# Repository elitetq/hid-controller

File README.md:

# hid-controller

A custom USB gamepad built on an STM32F103, with a KiCad PCB and STM32 firmware. It has two analog sticks with click switches, a D-pad, face buttons, bumpers, digital triggers and Start/Share buttons.

https://github.com/user-attachments/assets/c4e4d3e5-b4be-487b-b6eb-255510382f0a

## USB identity and compatibility

The device appears as **J-Controller**, with manufacturer **Jonart B** and VID:PID **1209:028e**. It sends custom HID gamepad reports. The controls follow an Xbox-style layout, but the firmware does not provide native XInput support.

Linux enumerates the controller. Windows only partly enumerates it so far. You can try [x360ce](https://www.x360ce.com/) for XInput mapping, but Windows needs to detect the controller first. There is no confirmed setup procedure for Windows yet.

## Files

| Path | Purpose |
| --- | --- |
| [hid-controller-pcb/](hid-controller-pcb/) | KiCad schematic, PCB, libraries and BOM |
| `hid-controller-pcb/production/hid-controller-pcb.zip` | Fabrication Gerbers |
| `hid-controller-code/hid-controller-code/` | Active firmware and Makefile |
| `Core/Src/main.c` inside the firmware folder | ADC sampling, button mapping and report updates |
| `USB_DEVICE/App/` inside the firmware folder | USB descriptors and HID interface |
| `usb-backup/` inside the firmware folder | Older firmware copy; not the Makefile's source tree |
| `assets/` | Photos, PCB layout and video |

## PCB and assembly

Open `hid-controller-pcb/hid-controller-pcb.kicad_pro` in KiCad. Review the schematic and layout before fabrication. The root board BOM is `hid-controller-pcb/BOM.csv`; production exports also include `production/bom.csv` and `production/positions.csv`. Match the BOM and placement export to the board revision you intend to assemble.

Use the schematic's **SWDIO**, **SWCLK** and ground nets for the ST-Link connection, together with target-voltage reference as required by your probe. Check the actual connector orientation against the schematic rather than assuming a standard header pin order.

## Build

Requires GNU make, Arm GNU tools (`arm-none-eabi-gcc`, `objcopy` and `size`, including the C library/nano specs), and a POSIX shell for Makefile commands. Flashing requires ST-Link and [STM32CubeProgrammer](https://www.st.com/en/development-tools/stm32cubeprog.html), with `STM32_Programmer_CLI` on PATH.

**NOTE:** The firmware folder contains both `STM32F103XX_FLASH.ld` and `STM32F103xx_FLASH.ld`. They collide on a normal Windows filesystem. Use a case-sensitive filesystem (for example, a clone inside WSL's Linux filesystem) so both files can be checked out. The Makefile selects `STM32F103xx_FLASH.ld`.

```sh
git clone https://github.com/elitetq/hid-controller.git
cd hid-controller/hid-controller-code/hid-controller-code
make clean
make
```

The compiler path defaults to `/usr/bin/`. If your toolchain is elsewhere:

```sh
make GCC_PATH=/path/to/arm-toolchain/bin
```

Or, if the Arm tools are already on PATH, use `make GCC_PATH=`. The output is `build/hid-controller-code.elf`, with `.hex` and `.bin` versions alongside it. Clean first so checked-in build artifacts are not reused. There is no specific compiler/programmer version recorded for this build.

## Flash

Connect ST-Link to the powered target with common ground. From the firmware folder:

```sh
STM32_Programmer_CLI -c port=SWD -w build/hid-controller-code.elf -v -rst
```

This writes the ELF, verifies it and resets the device. The Makefile's `make flash` target contains a machine-specific Windows programmer path; use the command above or override `STMJLINKPATH` with your programmer executable. If you build in WSL, make sure the programmer can access ST-Link. You can also copy the ELF to Windows and flash it with STM32CubeProgrammer there.

## Check the inputs

1. Connect the controller's USB data port to the host. On Linux, `lsusb -d 1209:028e` can check enumeration; then check the inputs separately.
2. Open a gamepad input viewer. On Windows, start with **Win+R > joy.cpl** if the device appears there.
3. Move both sticks through their range and back to center. Check the D-pad, face buttons, bumpers, Start/Share and both stick clicks individually.
4. Press and release each trigger. These are digital switches: the firmware maps each trigger to 0 or 255, not an analog pressure range.
5. If using x360ce, confirm it detects the source device before mapping controls to a virtual controller and testing in a game. Failure to enumerate must be solved before mapping can help.

If inputs are missing, compare `gamepad_update_buttons()` and `gamepad_update_joysticks()` in `Core/Src/main.c` with the schematic and the report descriptor in `USB_DEVICE/App/usbd_custom_hid_if.c`. The two stick axes are swapped/inverted in software. Check the inputs on the assembled controller, as enumeration alone does not confirm that the mappings work.

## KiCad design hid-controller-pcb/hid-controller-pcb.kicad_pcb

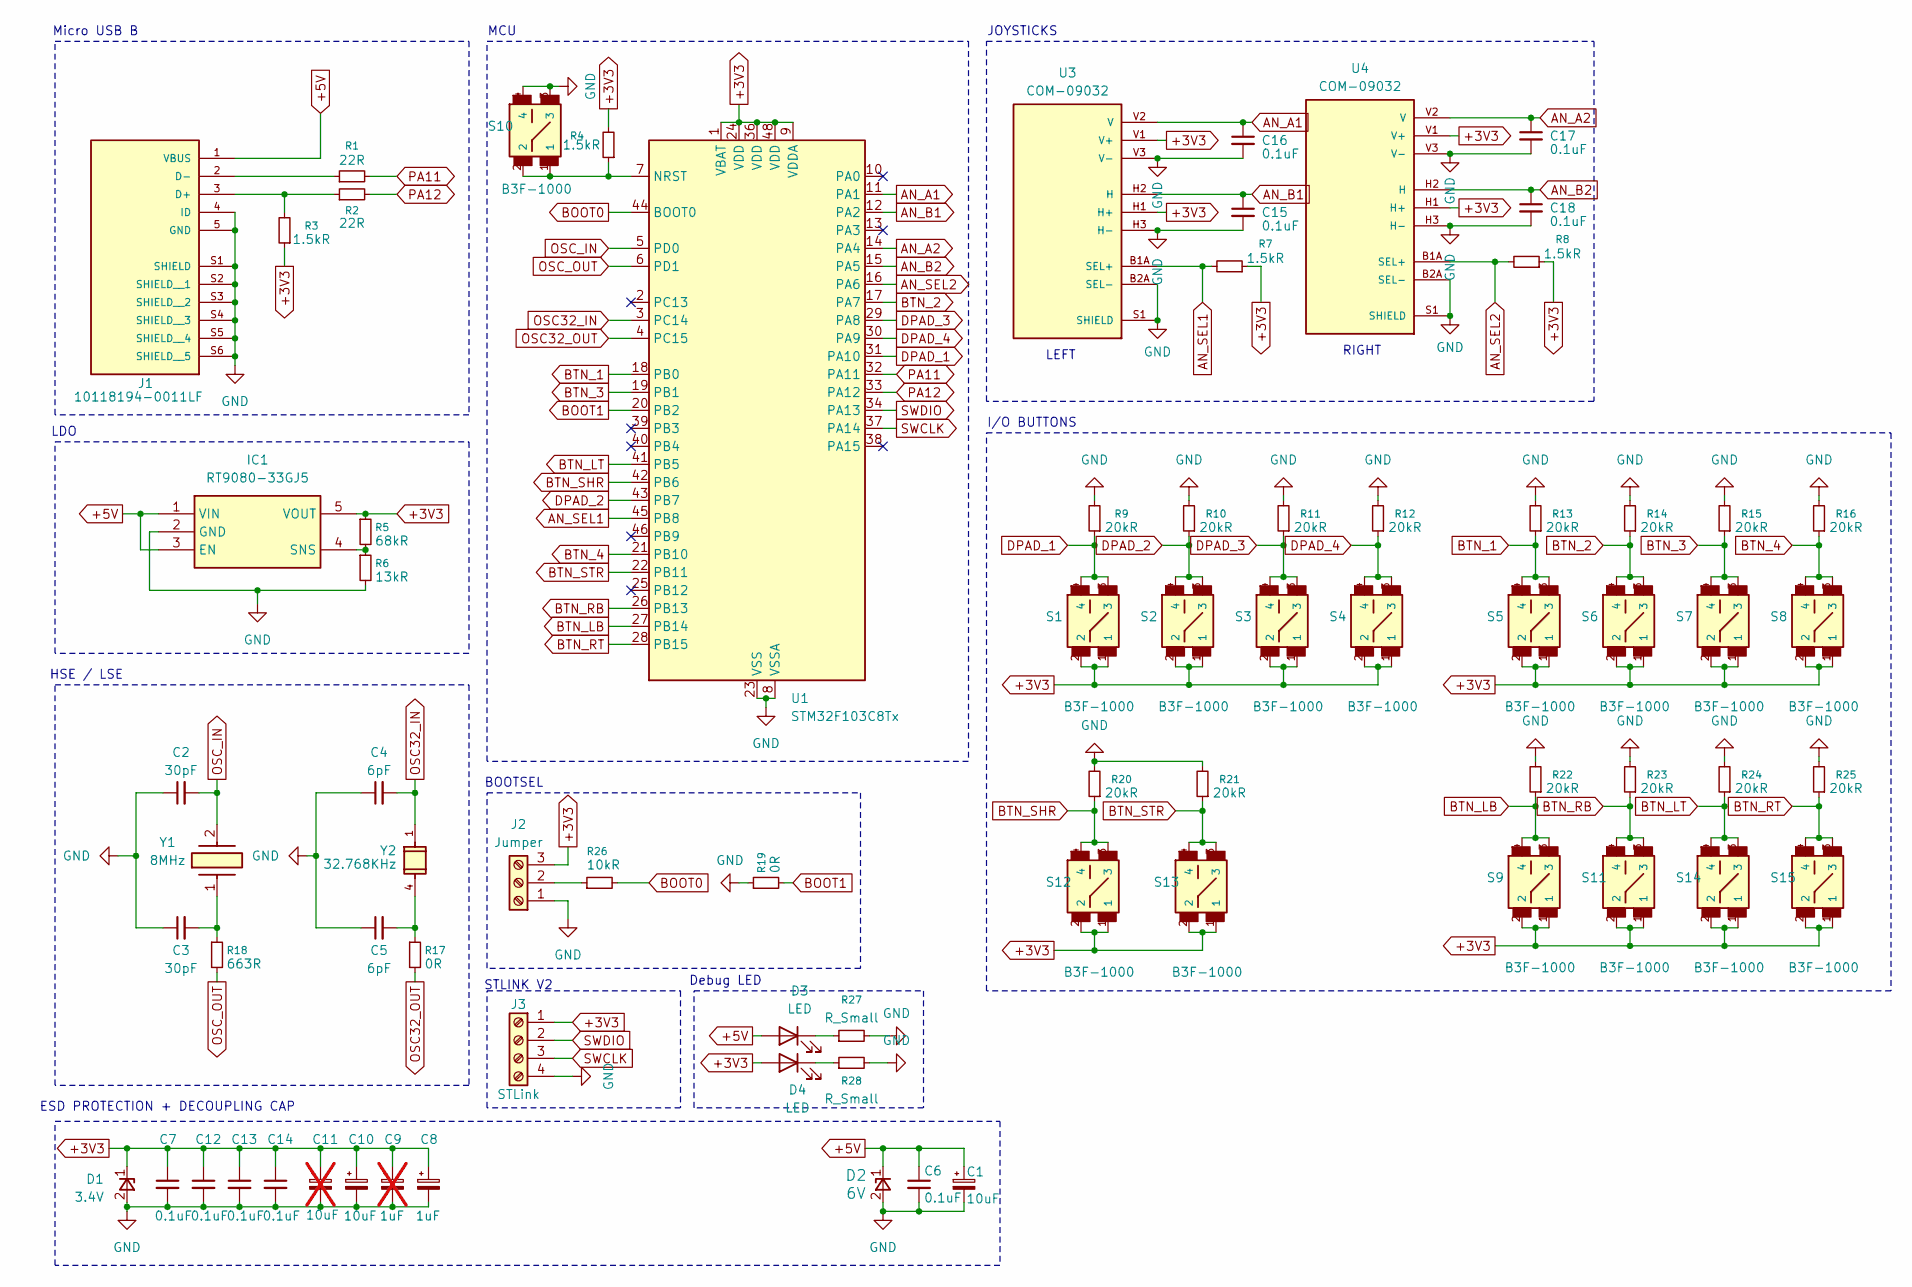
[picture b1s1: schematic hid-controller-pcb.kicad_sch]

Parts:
C1, C10: 10uF; CAPAE530X550N
C2, C3: 30pF; C_0603_1608Metric
C4, C5: 6pF; C_0603_1608Metric
C6, C7, C12, C13, C14: 0.1uF; C_0603_1608Metric
C8: 1uF; C_0603_1608Metric
C9: 1uF; C_0603_1608Metric; not fitted
C11: 10uF; CAPAE530X550N; not fitted
C15, C16, C17, C18: 0.1uF; C_0805_2012Metric_Pad1.18x1.45mm_HandSolder
D1: 3.4V; SMFA2005CA; Manufacturer_Part_Number SMF3.3; Mouser Part Number 576-SMF3.3
D2: 6V; DIODE_VESD05A1B-HD1-GS08_VIS
D3, D4: LED; LED_0805_2012Metric
IC1: RT9080-33GJ5; Manufacturer_Part_Number RT9080-33GJ5; Mouser Part Number 835-RT9080-33GJ5
J1: 10118194-0011LF; PARTREV D
J2: Jumper; PinHeader_1x03_P2.54mm_Vertical
J3: STLink; PinHeader_1x04_P2.54mm_Vertical
R1, R2: 22R; R_0805_2012Metric_Pad1.20x1.40mm_HandSolder
R3, R4, R7, R8: 1.5kR; R_0603_1608Metric
R5: 68kR; R_0603_1608Metric
R6: 13kR; R_0603_1608Metric
R9, R10, R11, R12, R13, R14, R15, R16, R20, R21, R22, R23, R24, R25: 20kR; R_0603_1608Metric
R17, R19: 0R; R_0603_1608Metric
R18: 663R; R_0603_1608Metric
R26: 10kR; R_0805_2012Metric_Pad1.20x1.40mm_HandSolder
R27, R28: R_Small; R_0805_2012Metric_Pad1.20x1.40mm_HandSolder
S1, S2, S3, S4, S5, S6, S7, S8, S9, S10, S11, S12, S13, S14, S15: B3F-1000; SW_B3F-1000
U1: STM32F103C8Tx; LQFP-48_7x7mm_P0.5mm
U3, U4: COM-09032; XDCR_COM-09032; PARTREV N/A
Y1: 8MHz; ABLS-8.000MHZ-B4-T; Manufacturer_Part_Number ABLS-8.000MHZ-B4-T; Mouser Part Number 815-ABLS-8.0M-T
Y2: 32.768KHz; XTAL_ABS25-32.768KHZ-6-T

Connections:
+3V3: C7.1, C8.1, C9.1, C10.1, C11.1, C12.1, C13.1, C14.1, D1.1 (K), D4.2 (A), IC1.5 (VOUT), J2.3, J3.1, R3.1, R4.2, R5.1, R7.1, R8.1, S1.1, S1.2, S2.1, S2.2, S3.1, S3.2, S4.1, S4.2, S5.1, S5.2, S6.1, S6.2, S7.1, S7.2, S8.1, S8.2, S9.1, S9.2, S11.1, S11.2, S12.1, S12.2, S13.1, S13.2, S14.1, S14.2, S15.1, S15.2, U1.1 (VBAT), U1.9 (VDDA), U1.24 (VDD), U1.36 (VDD), U1.48 (VDD), U3.H1 (H+), U3.V1 (V+), U4.H1 (H+), U4.V1 (V+)
+5V: C1.1, C6.1, D2.1, D3.2 (A), IC1.1 (VIN), IC1.3 (EN), J1.1 (VBUS)
AN_A1: C16.1, U1.11 (PA1), U3.V2 (V)
AN_A2: C17.1, U1.14 (PA4), U4.V2 (V)
AN_B1: C15.1, U1.12 (PA2), U3.H2 (H)
AN_B2: C18.1, U1.15 (PA5), U4.H2 (H)
AN_SEL1: R7.2, U1.45 (PB8), U3.B1A (SEL+)
AN_SEL2: R8.2, U1.16 (PA6), U4.B1A (SEL+)
BOOT0: R26.2, U1.44 (BOOT0)
BOOT1: R19.2, U1.20 (PB2)
BTN_1: R13.1, S5.3, S5.4, U1.18 (PB0)
BTN_2: R14.1, S6.3, S6.4, U1.17 (PA7)
BTN_3: R15.1, S7.3, S7.4, U1.19 (PB1)
BTN_4: R16.1, S8.3, S8.4, U1.21 (PB10)
BTN_LB: R22.1, S9.3, S9.4, U1.27 (PB14)
BTN_LT: R24.1, S14.3, S14.4, U1.41 (PB5)
BTN_RB: R23.1, S11.3, S11.4, U1.26 (PB13)
BTN_RT: R25.1, S15.3, S15.4, U1.28 (PB15)
BTN_SHR: R20.1, S12.3, S12.4, U1.42 (PB6)
BTN_STR: R21.1, S13.3, S13.4, U1.22 (PB11)
DPAD_1: R9.1, S1.3, S1.4, U1.31 (PA10)
DPAD_2: R10.1, S2.3, S2.4, U1.43 (PB7)
DPAD_3: R11.1, S3.3, S3.4, U1.29 (PA8)
DPAD_4: R12.1, S4.3, S4.4, U1.30 (PA9)
GND: C1.2, C2.1, C3.1, C4.1, C5.1, C6.2, C7.2, C8.2, C9.2, C10.2, C11.2, C12.2, C13.2, C14.2, C15.2, C16.2, C17.2, C18.2, D1.2 (A), D2.2, IC1.2 (GND), J1.4 (ID), J1.5 (GND), J1.S1 (SHIELD), J1.S2 (SHIELD__1), J1.S3 (SHIELD__2), J1.S4 (SHIELD__3), J1.S5 (SHIELD__4), J1.S6 (SHIELD__5), J2.1, J3.4, R6.2, R9.2, R10.2, R11.2, R12.2, R13.2, R14.2, R15.2, R16.2, R19.1, R20.2, R21.2, R22.2, R23.2, R24.2, R25.2, R27.2, R28.2, S10.3, S10.4, U1.8 (VSSA), U1.23 (VSS), U1.35 (VSS), U1.47 (VSS), U3.B2A (SEL-), U3.H3 (H-), U3.S1 (SHIELD), U3.S2 (SHIELD), U3.S3 (SHIELD), U3.S4 (SHIELD), U3.V3 (V-), U4.B2A (SEL-), U4.H3 (H-), U4.S1 (SHIELD), U4.S2 (SHIELD), U4.S3 (SHIELD), U4.S4 (SHIELD), U4.V3 (V-)
unnamed: C3.2, R18.1, Y1.1
unnamed: C5.2, R17.1, Y2.4
unnamed: D3.1 (K), R27.1
unnamed: D4.1 (K), R28.1
unnamed: IC1.4 (SNS), R5.2, R6.1
unnamed: J1.3 (D+), R2.1, R3.2
unnamed: J1.2 (D-), R1.1
unnamed: J2.2, R26.1
unnamed: R4.1, S10.1, S10.2, U1.7 (NRST)
OSC32_IN: C4.2, U1.3 (PC14), Y2.1
OSC32_OUT: R17.2, U1.4 (PC15)
OSC_IN: C2.2, U1.5 (PD0), Y1.2
OSC_OUT: R18.2, U1.6 (PD1)
PA11: R1.2, U1.32 (PA11)
PA12: R2.2, U1.33 (PA12)
SWCLK: J3.3, U1.37 (PA14)
SWDIO: J3.2, U1.34 (PA13)

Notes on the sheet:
MCU
Micro USB B
BOOTSEL
HSE / LSE
Debug LED
STLINK V2
RIGHT
LDO
LEFT
JOYSTICKS
I/O BUTTONS
ESD PROTECTION + DECOUPLING CAP

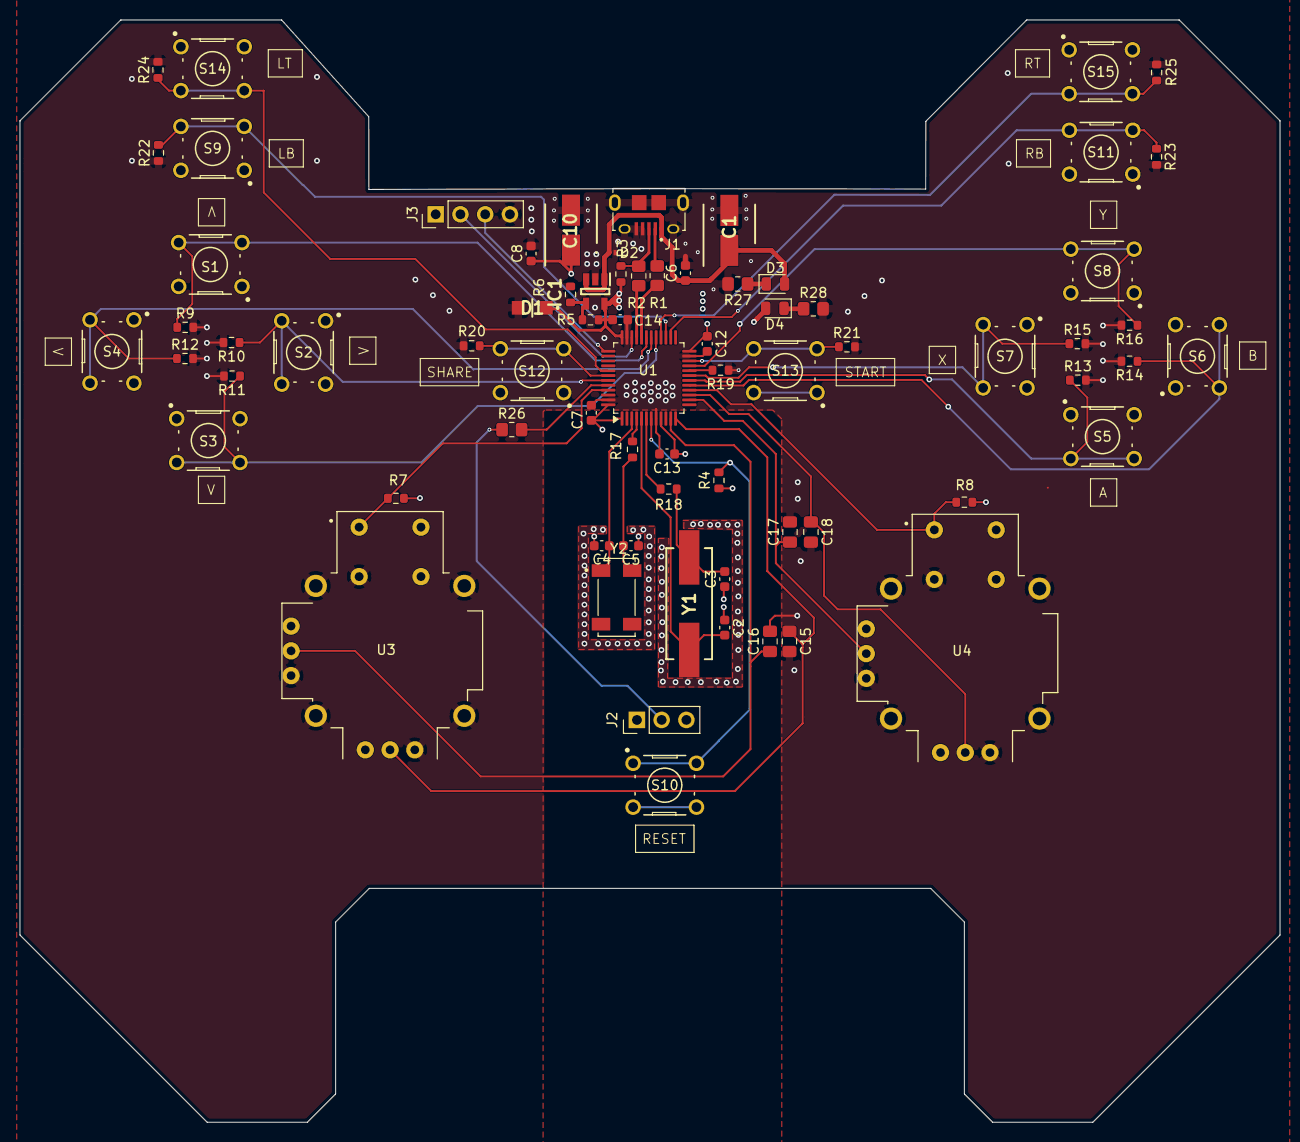
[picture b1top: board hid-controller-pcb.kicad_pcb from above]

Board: 4 copper layers, 129.3 x 113.2 mm, 72 parts (0 on the bottom side), 42 nets.

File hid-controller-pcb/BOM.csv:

Reference,Value,MPN,QTY
"C8,C9,C10,C11",10uF,CAPAE530X550N,4
"C2,C3",30pF,06031U300GAT2A,2
"C4,C5",6pF,CBR06C609CAGAC,2
"C6,C7,C12,C13,C14",0.1uF,C0603C104K5RACTU,5
D1,3.4V,SMF3.3,1
D2,6V,VESD05A1B-HD1-GS08,1
IC1,RT9080-33GJ5,RT9080-33GJ5,1
J1,10118194-0011LF,10118194-0011LF,1
J2,Jumper,PRPC003SAAN-RC,1
"R1,R2",22R,RC0805FR-0722RL,2
"R3,R4,R7,R8",1.5kR,RMCF0603FT1K50,4
R5,68kR,RC0603FR-0768KL,1
R6,13kR,RMCF0603FT13K0,1
"R9,R10,R11,R12,R13,R14,R15,R16",20kR,RC0603FR-0720KL,8
"R17,R19",0R,RC0603JR-070RL,2
R18,663R,RC0603FR-07665RL,1
"S1,S2,S3,S4,S5,S6,S7,S8,S10",B3F-1000,B3F-1000,12
U1,STM32F103C8Tx,STM32F103C8Tx,1
"U3,U4",COM-09032,9032,2
Y1,8MHz,ABLS-8.000MHZ-B4-T,1
Y2,32.768KHz,ABS25-32.768KHZ-6-T,1
C1,1uF,UMK107AB7105KA-T,1
,jumper short,QPC02SXGN-RC,1

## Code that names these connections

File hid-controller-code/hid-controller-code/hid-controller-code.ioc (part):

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Mcu.Name=STM32F103C(8-B)Tx
Mcu.Package=LQFP48
Mcu.UserName=STM32F103C8Tx
PA1.Signal=ADCx_IN1
PA10.Signal=GPIO_Input
PA11.Mode=Device
PA11.Signal=USB_DM
PA12.Mode=Device
PA12.Signal=USB_DP
PA13.Mode=Serial_Wire
PA13.Signal=SYS_JTMS-SWDIO
PA14.Mode=Serial_Wire
PA14.Signal=SYS_JTCK-SWCLK
PA2.Signal=ADCx_IN2
PA4.Signal=ADCx_IN4
PA5.Signal=ADCx_IN5
PA6.GPIOParameters=GPIO_PuPd
PA6.GPIO_PuPd=GPIO_PULLDOWN
PA6.Signal=GPIO_Input
PA7.Signal=GPIO_Input
PA8.GPIOParameters=GPIO_PuPd
PA8.GPIO_PuPd=GPIO_NOPULL
PA8.Signal=GPIO_Input
PA9.GPIOParameters=GPIO_PuPd
PA9.GPIO_PuPd=GPIO_NOPULL
PA9.Signal=GPIO_Input
PB0.Signal=GPIO_Input
PB1.Signal=GPIO_Input
PB10.Signal=GPIO_Input
PB11.Signal=GPIO_Input
PB13.Signal=GPIO_Input
PB14.GPIOParameters=GPIO_PuPd
PB14.GPIO_PuPd=GPIO_NOPULL
PB14.Signal=GPIO_Input
PB15.Signal=GPIO_Input
PB5.Signal=GPIO_Input
PB6.Signal=GPIO_Input
PB7.Signal=GPIO_Input
PB8.GPIOParameters=GPIO_PuPd
PB8.GPIO_PuPd=GPIO_PULLDOWN
PB8.Signal=GPIO_Input
PC14-OSC32_IN.Mode=LSE-External-Oscillator
PC14-OSC32_IN.Signal=RCC_OSC32_IN
PC15-OSC32_OUT.Mode=LSE-External-Oscillator
PC15-OSC32_OUT.Signal=RCC_OSC32_OUT
PD0-OSC_IN.Mode=HSE-External-Oscillator
PD0-OSC_IN.Signal=RCC_OSC_IN
PD1-OSC_OUT.Mode=HSE-External-Oscillator
PD1-OSC_OUT.Signal=RCC_OSC_OUT
RCC.SYSCLKFreq_VALUE=72000000
RCC.SYSCLKSource=RCC_SYSCLKSOURCE_PLLCLK
board=custom
